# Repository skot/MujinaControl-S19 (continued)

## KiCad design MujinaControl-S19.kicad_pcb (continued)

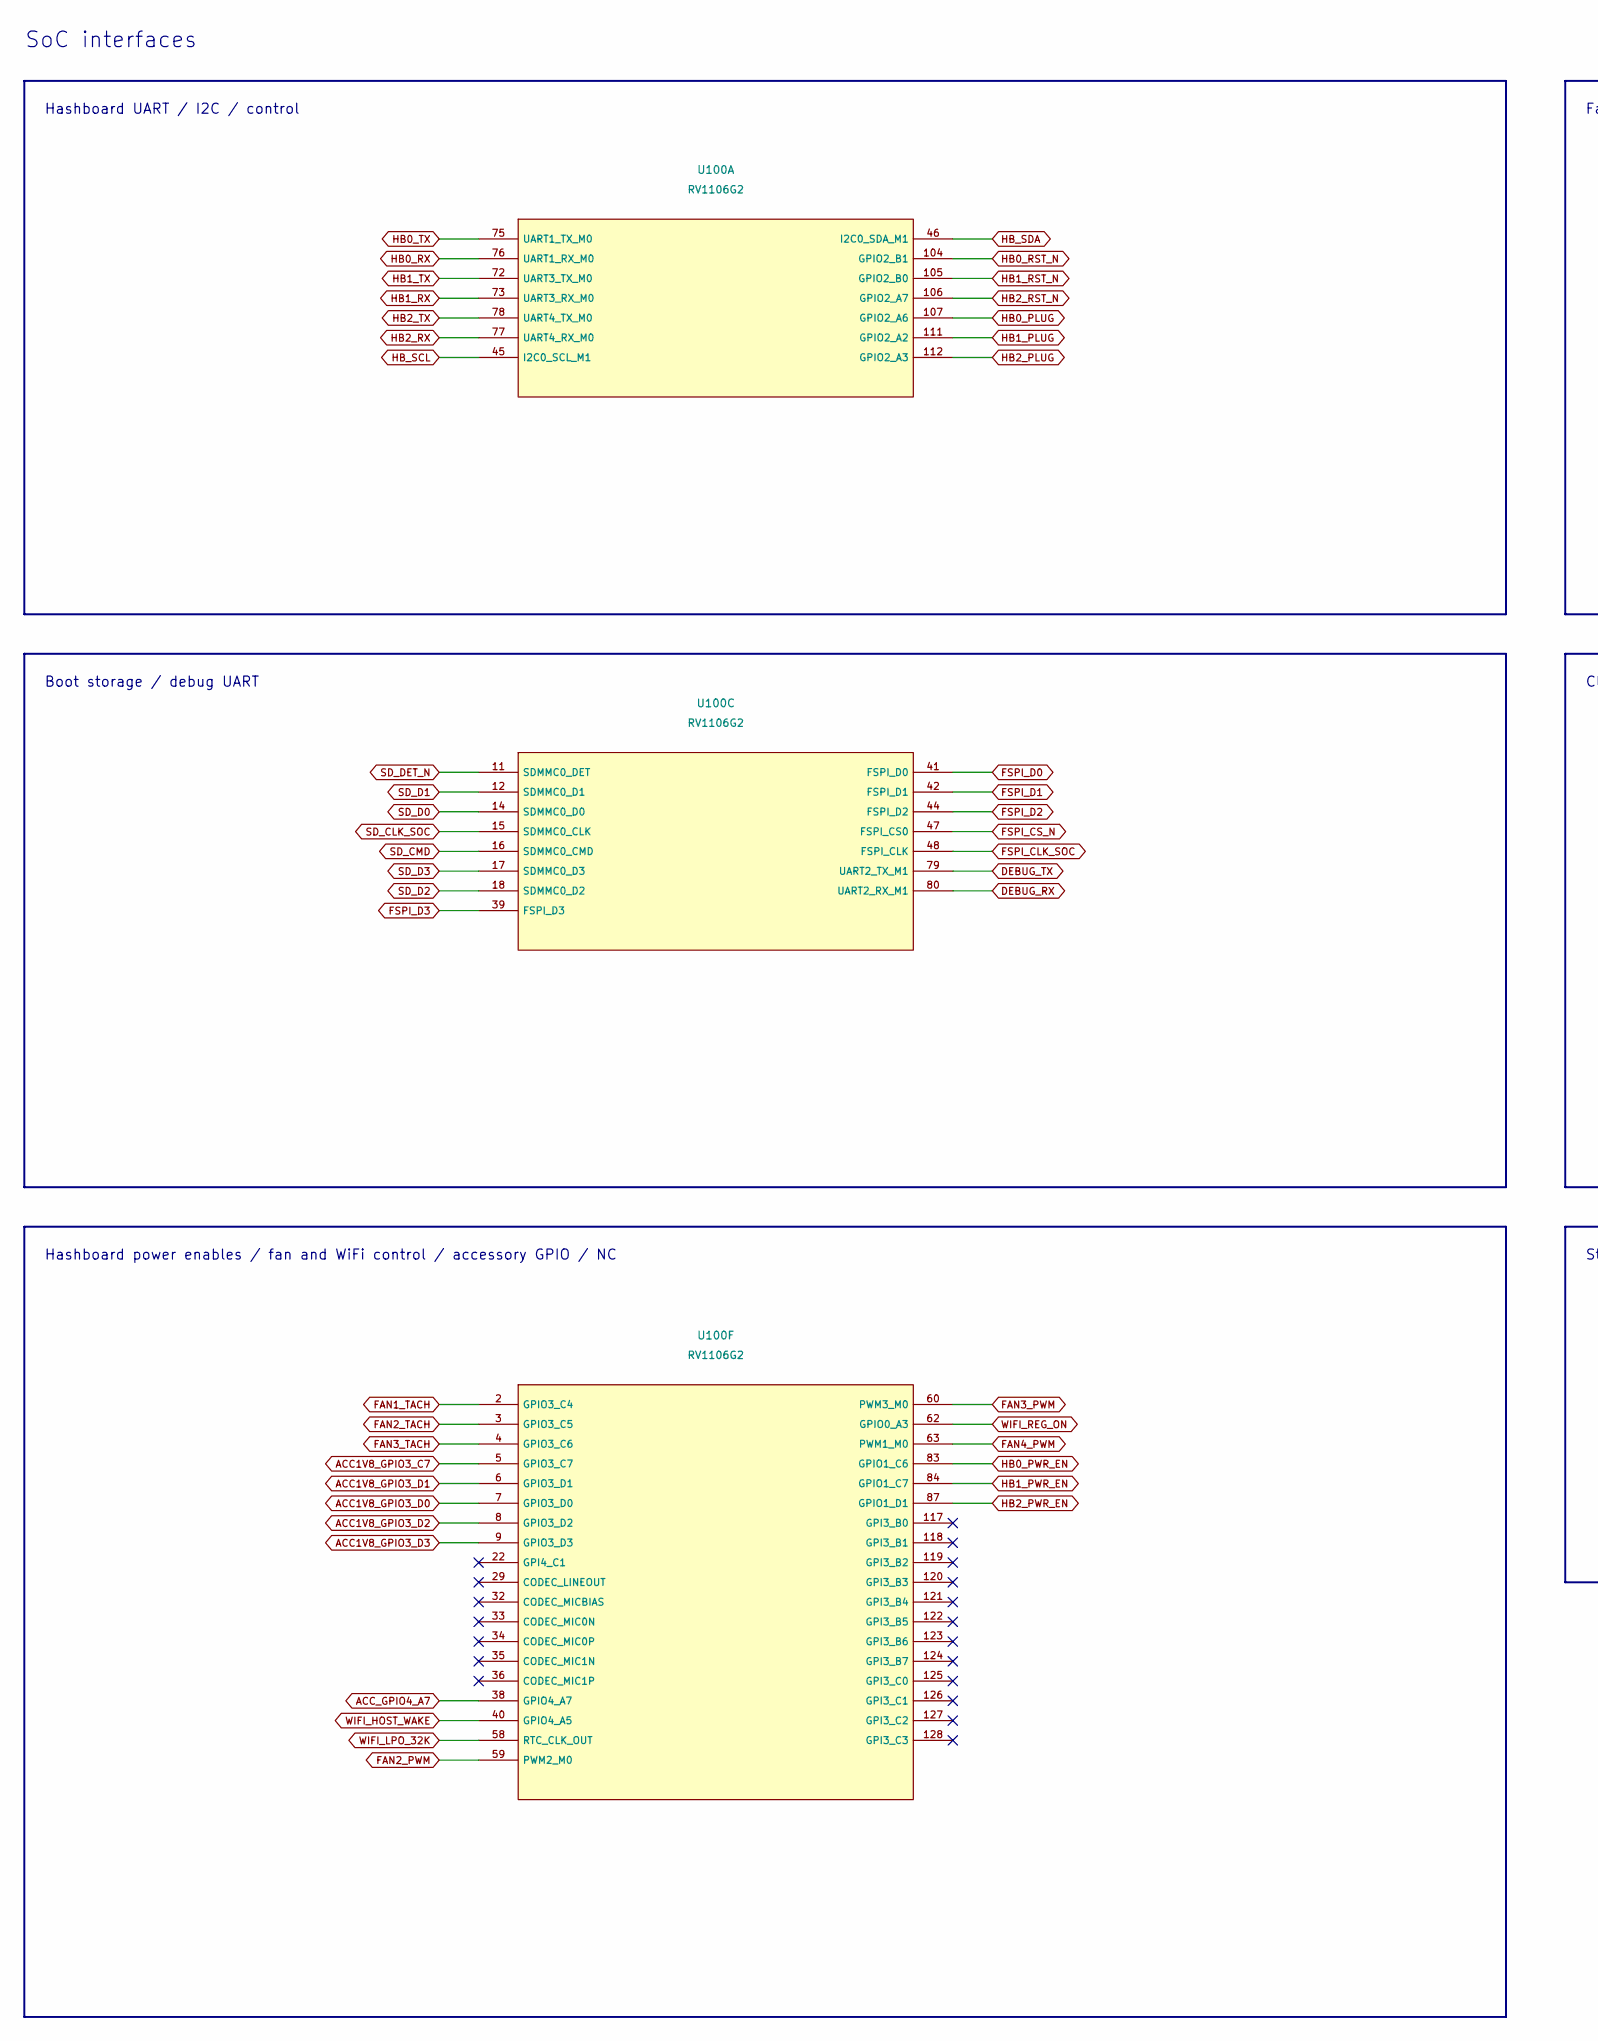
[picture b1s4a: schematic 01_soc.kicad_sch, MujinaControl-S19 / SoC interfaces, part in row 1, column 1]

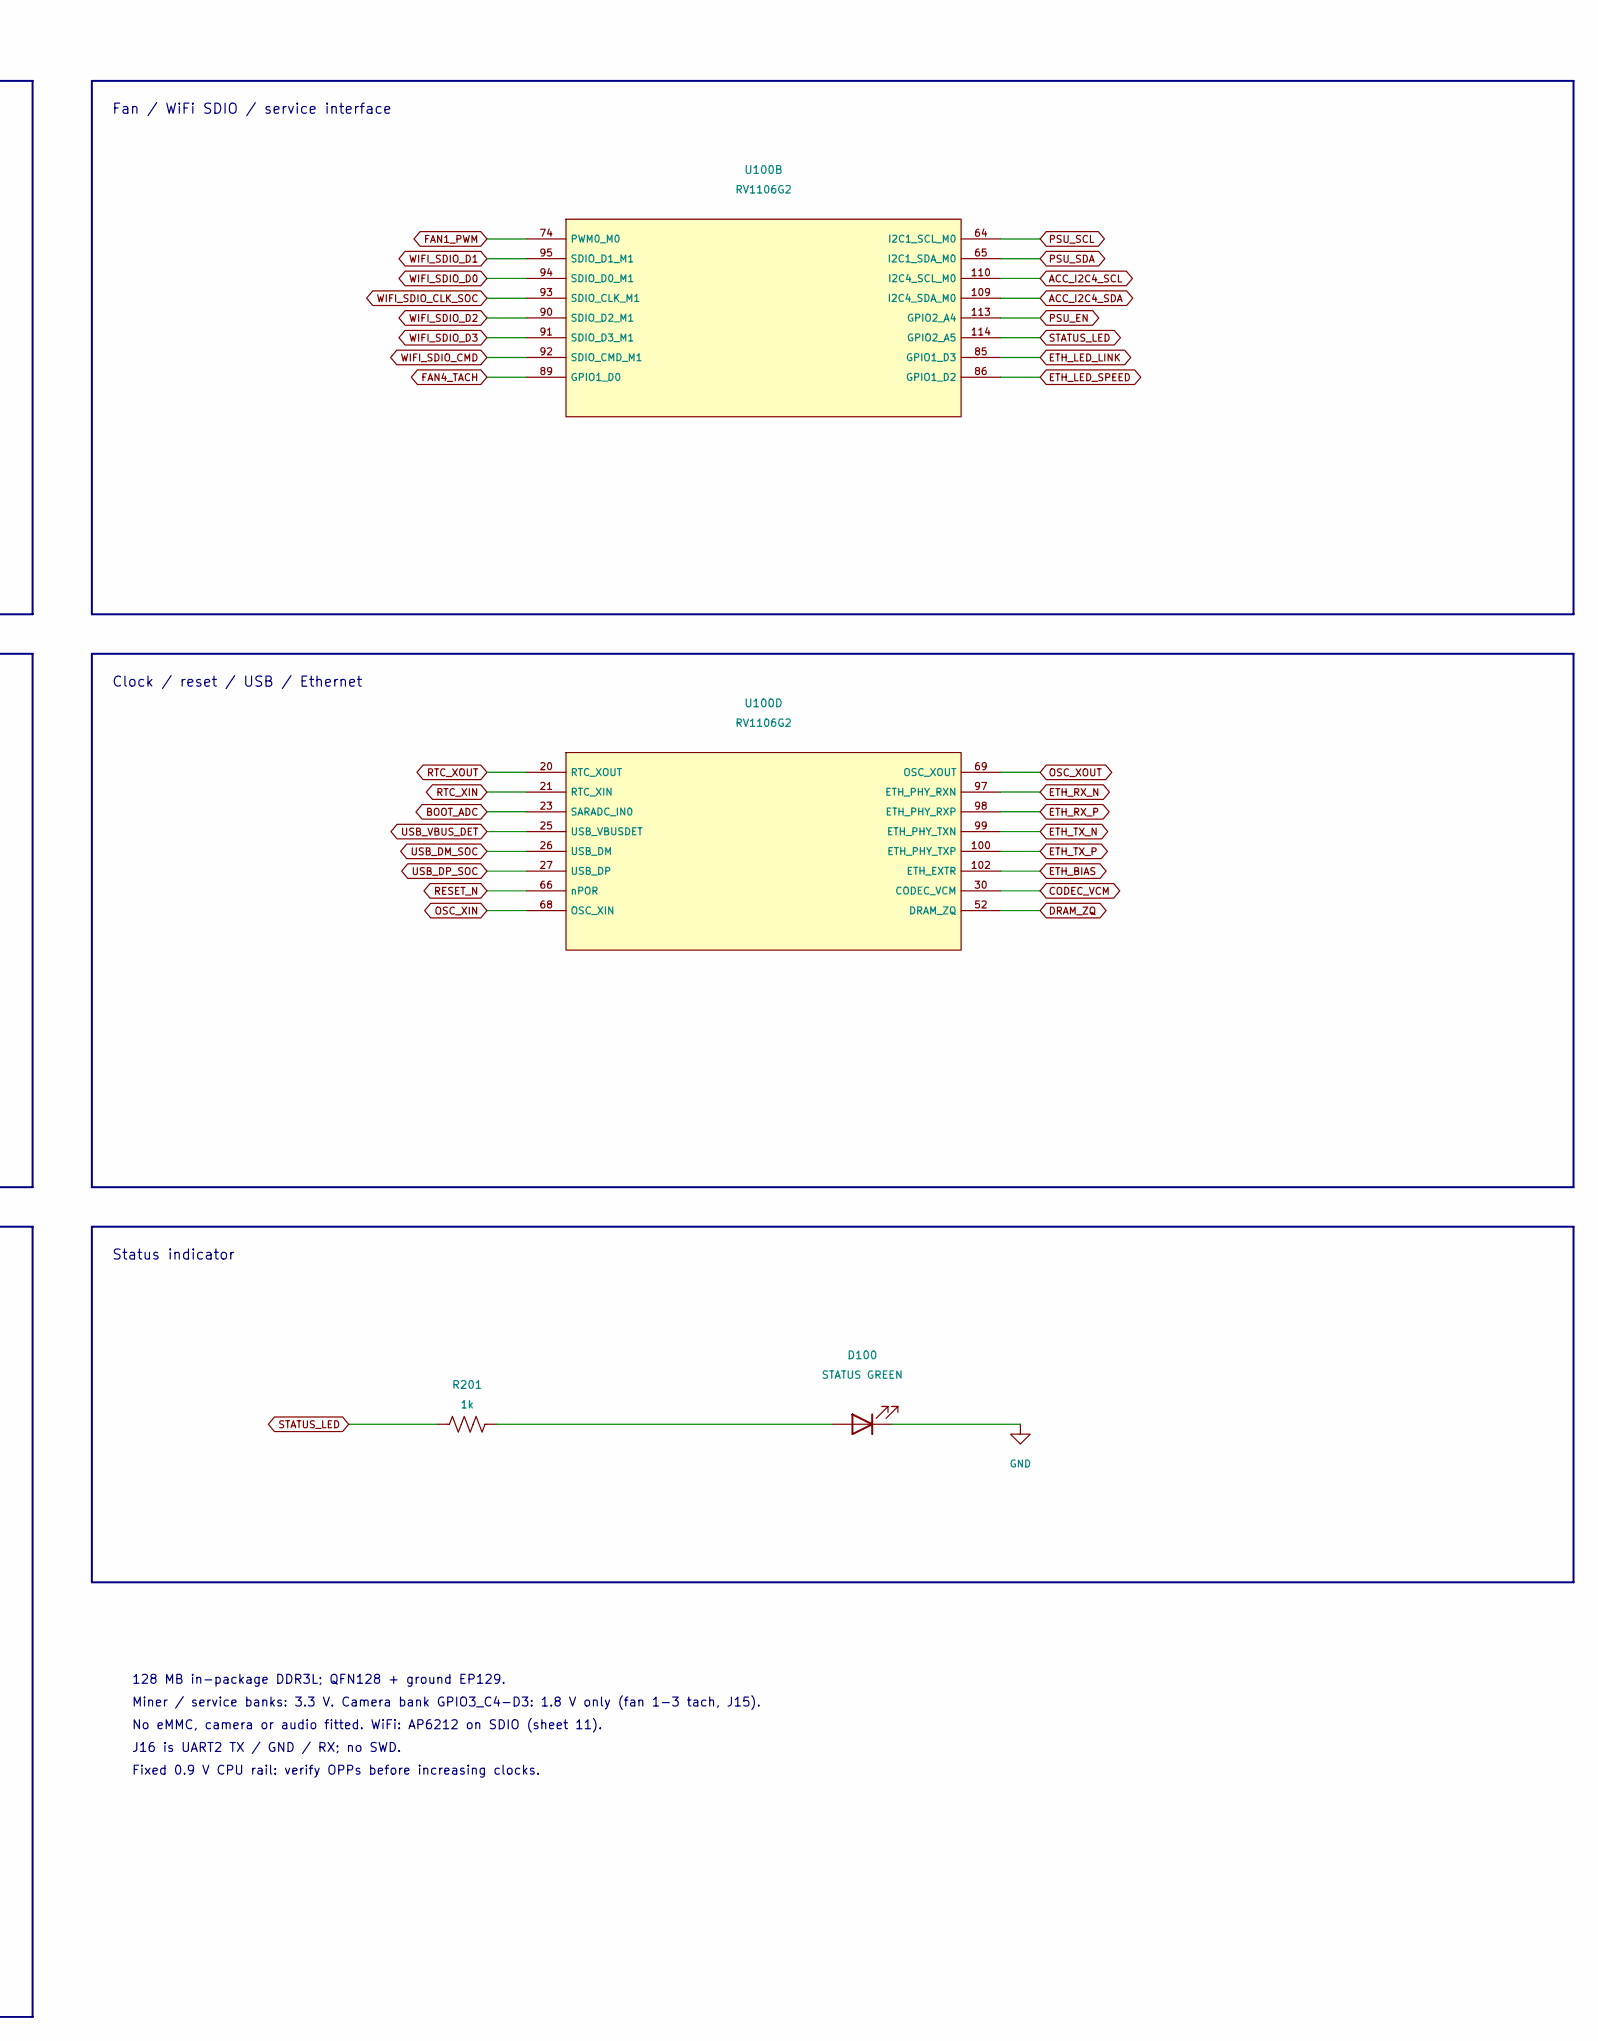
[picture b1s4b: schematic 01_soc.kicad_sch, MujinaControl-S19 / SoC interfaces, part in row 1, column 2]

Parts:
D100: STATUS GREEN; LED_0603_1608Metric; MPN LTST-C190KGKT; LCSC C125094
R201: 1k; R_0402_1005Metric; MPN 0402WGF1001TCE; LCSC C11702
U100: RV1106G2; Rockchip_QFN-128-1EP_12.3x12.3mm_P0.35mm_EP7x7mm; MPN RV1106G2; LCSC C5272606

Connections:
ACC1V8_GPIO3_C7: U100.5 (GPIO3_C7); also elsewhere on the board
ACC1V8_GPIO3_D0: U100.7 (GPIO3_D0); also elsewhere on the board
ACC1V8_GPIO3_D1: U100.6 (GPIO3_D1); also elsewhere on the board
ACC1V8_GPIO3_D2: U100.8 (GPIO3_D2); also elsewhere on the board
ACC1V8_GPIO3_D3: U100.9 (GPIO3_D3); also elsewhere on the board
ACC_GPIO4_A7: U100.38 (GPIO4_A7); also elsewhere on the board
ACC_I2C4_SCL: U100.110 (I2C4_SCL_M0); also elsewhere on the board
ACC_I2C4_SDA: U100.109 (I2C4_SDA_M0); also elsewhere on the board
BOOT_ADC: U100.23 (SARADC_IN0); also elsewhere on the board
CODEC_VCM: U100.30 (CODEC_VCM); also elsewhere on the board
DEBUG_RX: U100.80 (UART2_RX_M1); also elsewhere on the board
DEBUG_TX: U100.79 (UART2_TX_M1); also elsewhere on the board
DRAM_ZQ: U100.52 (DRAM_ZQ); also elsewhere on the board
ETH_BIAS: U100.102 (ETH_EXTR); also elsewhere on the board
ETH_LED_LINK: U100.85 (GPIO1_D3); also elsewhere on the board
ETH_LED_SPEED: U100.86 (GPIO1_D2); also elsewhere on the board
ETH_RX_N: U100.97 (ETH_PHY_RXN); also elsewhere on the board
ETH_RX_P: U100.98 (ETH_PHY_RXP); also elsewhere on the board
ETH_TX_N: U100.99 (ETH_PHY_TXN); also elsewhere on the board
ETH_TX_P: U100.100 (ETH_PHY_TXP); also elsewhere on the board
FAN1_PWM: U100.74 (PWM0_M0); also elsewhere on the board
FAN1_TACH: U100.2 (GPIO3_C4); also elsewhere on the board
FAN2_PWM: U100.59 (PWM2_M0); also elsewhere on the board
FAN2_TACH: U100.3 (GPIO3_C5); also elsewhere on the board
FAN3_PWM: U100.60 (PWM3_M0); also elsewhere on the board
FAN3_TACH: U100.4 (GPIO3_C6); also elsewhere on the board
FAN4_PWM: U100.63 (PWM1_M0); also elsewhere on the board
FAN4_TACH: U100.89 (GPIO1_D0); also elsewhere on the board
FSPI_CLK_SOC: U100.48 (FSPI_CLK); also elsewhere on the board
FSPI_CS_N: U100.47 (FSPI_CS0); also elsewhere on the board
FSPI_D0: U100.41 (FSPI_D0); also elsewhere on the board
FSPI_D1: U100.42 (FSPI_D1); also elsewhere on the board
FSPI_D2: U100.44 (FSPI_D2); also elsewhere on the board
FSPI_D3: U100.39 (FSPI_D3); also elsewhere on the board
GND: D100.1 (K); also elsewhere on the board
HB0_PLUG: U100.107 (GPIO2_A6); also elsewhere on the board
HB0_PWR_EN: U100.83 (GPIO1_C6); also elsewhere on the board
HB0_RST_N: U100.104 (GPIO2_B1); also elsewhere on the board
HB0_RX: U100.76 (UART1_RX_M0); also elsewhere on the board
HB0_TX: U100.75 (UART1_TX_M0); also elsewhere on the board
HB1_PLUG: U100.111 (GPIO2_A2); also elsewhere on the board
HB1_PWR_EN: U100.84 (GPIO1_C7); also elsewhere on the board
HB1_RST_N: U100.105 (GPIO2_B0); also elsewhere on the board
HB1_RX: U100.73 (UART3_RX_M0); also elsewhere on the board
HB1_TX: U100.72 (UART3_TX_M0); also elsewhere on the board
HB2_PLUG: U100.112 (GPIO2_A3); also elsewhere on the board
HB2_PWR_EN: U100.87 (GPIO1_D1); also elsewhere on the board
HB2_RST_N: U100.106 (GPIO2_A7); also elsewhere on the board
HB2_RX: U100.77 (UART4_RX_M0); also elsewhere on the board
HB2_TX: U100.78 (UART4_TX_M0); also elsewhere on the board
HB_SCL: U100.45 (I2C0_SCL_M1); also elsewhere on the board
HB_SDA: U100.46 (I2C0_SDA_M1); also elsewhere on the board
unnamed: D100.2 (A), R201.2
OSC_XIN: U100.68 (OSC_XIN); also elsewhere on the board
OSC_XOUT: U100.69 (OSC_XOUT); also elsewhere on the board
PSU_EN: U100.113 (GPIO2_A4); also elsewhere on the board
PSU_SCL: U100.64 (I2C1_SCL_M0); also elsewhere on the board
PSU_SDA: U100.65 (I2C1_SDA_M0); also elsewhere on the board
RESET_N: U100.66 (nPOR); also elsewhere on the board
RTC_XIN: U100.21 (RTC_XIN); also elsewhere on the board
RTC_XOUT: U100.20 (RTC_XOUT); also elsewhere on the board
SD_CLK_SOC: U100.15 (SDMMC0_CLK); also elsewhere on the board
SD_CMD: U100.16 (SDMMC0_CMD); also elsewhere on the board
SD_D0: U100.14 (SDMMC0_D0); also elsewhere on the board
SD_D1: U100.12 (SDMMC0_D1); also elsewhere on the board
SD_D2: U100.18 (SDMMC0_D2); also elsewhere on the board
SD_D3: U100.17 (SDMMC0_D3); also elsewhere on the board
SD_DET_N: U100.11 (SDMMC0_DET); also elsewhere on the board
STATUS_LED: R201.1, U100.114 (GPIO2_A5)
USB_DM_SOC: U100.26 (USB_DM); also elsewhere on the board
USB_DP_SOC: U100.27 (USB_DP); also elsewhere on the board
USB_VBUS_DET: U100.25 (USB_VBUSDET); also elsewhere on the board
WIFI_HOST_WAKE: U100.40 (GPIO4_A5); also elsewhere on the board
WIFI_LPO_32K: U100.58 (RTC_CLK_OUT); also elsewhere on the board
WIFI_REG_ON: U100.62 (GPIO0_A3); also elsewhere on the board
WIFI_SDIO_CLK_SOC: U100.93 (SDIO_CLK_M1); also elsewhere on the board
WIFI_SDIO_CMD: U100.92 (SDIO_CMD_M1); also elsewhere on the board
WIFI_SDIO_D0: U100.94 (SDIO_D0_M1); also elsewhere on the board
WIFI_SDIO_D1: U100.95 (SDIO_D1_M1); also elsewhere on the board
WIFI_SDIO_D2: U100.90 (SDIO_D2_M1); also elsewhere on the board
WIFI_SDIO_D3: U100.91 (SDIO_D3_M1); also elsewhere on the board

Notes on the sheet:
Clock / reset / USB / Ethernet
Status indicator
Fixed 0.9 V CPU rail: verify OPPs before increasing clocks.
Miner / service banks: 3.3 V. Camera bank GPIO3_C4-D3: 1.8 V only (fan 1-3 tach, J15).
Hashboard UART / I2C / control
No eMMC, camera or audio fitted. WiFi: AP6212 on SDIO (sheet 11).
Boot storage / debug UART
Hashboard power enables / fan and WiFi control / accessory GPIO / NC
J16 is UART2 TX / GND / RX; no SWD.
Fan / WiFi SDIO / service interface
128 MB in-package DDR3L; QFN128 + ground EP129.
SoC interfaces

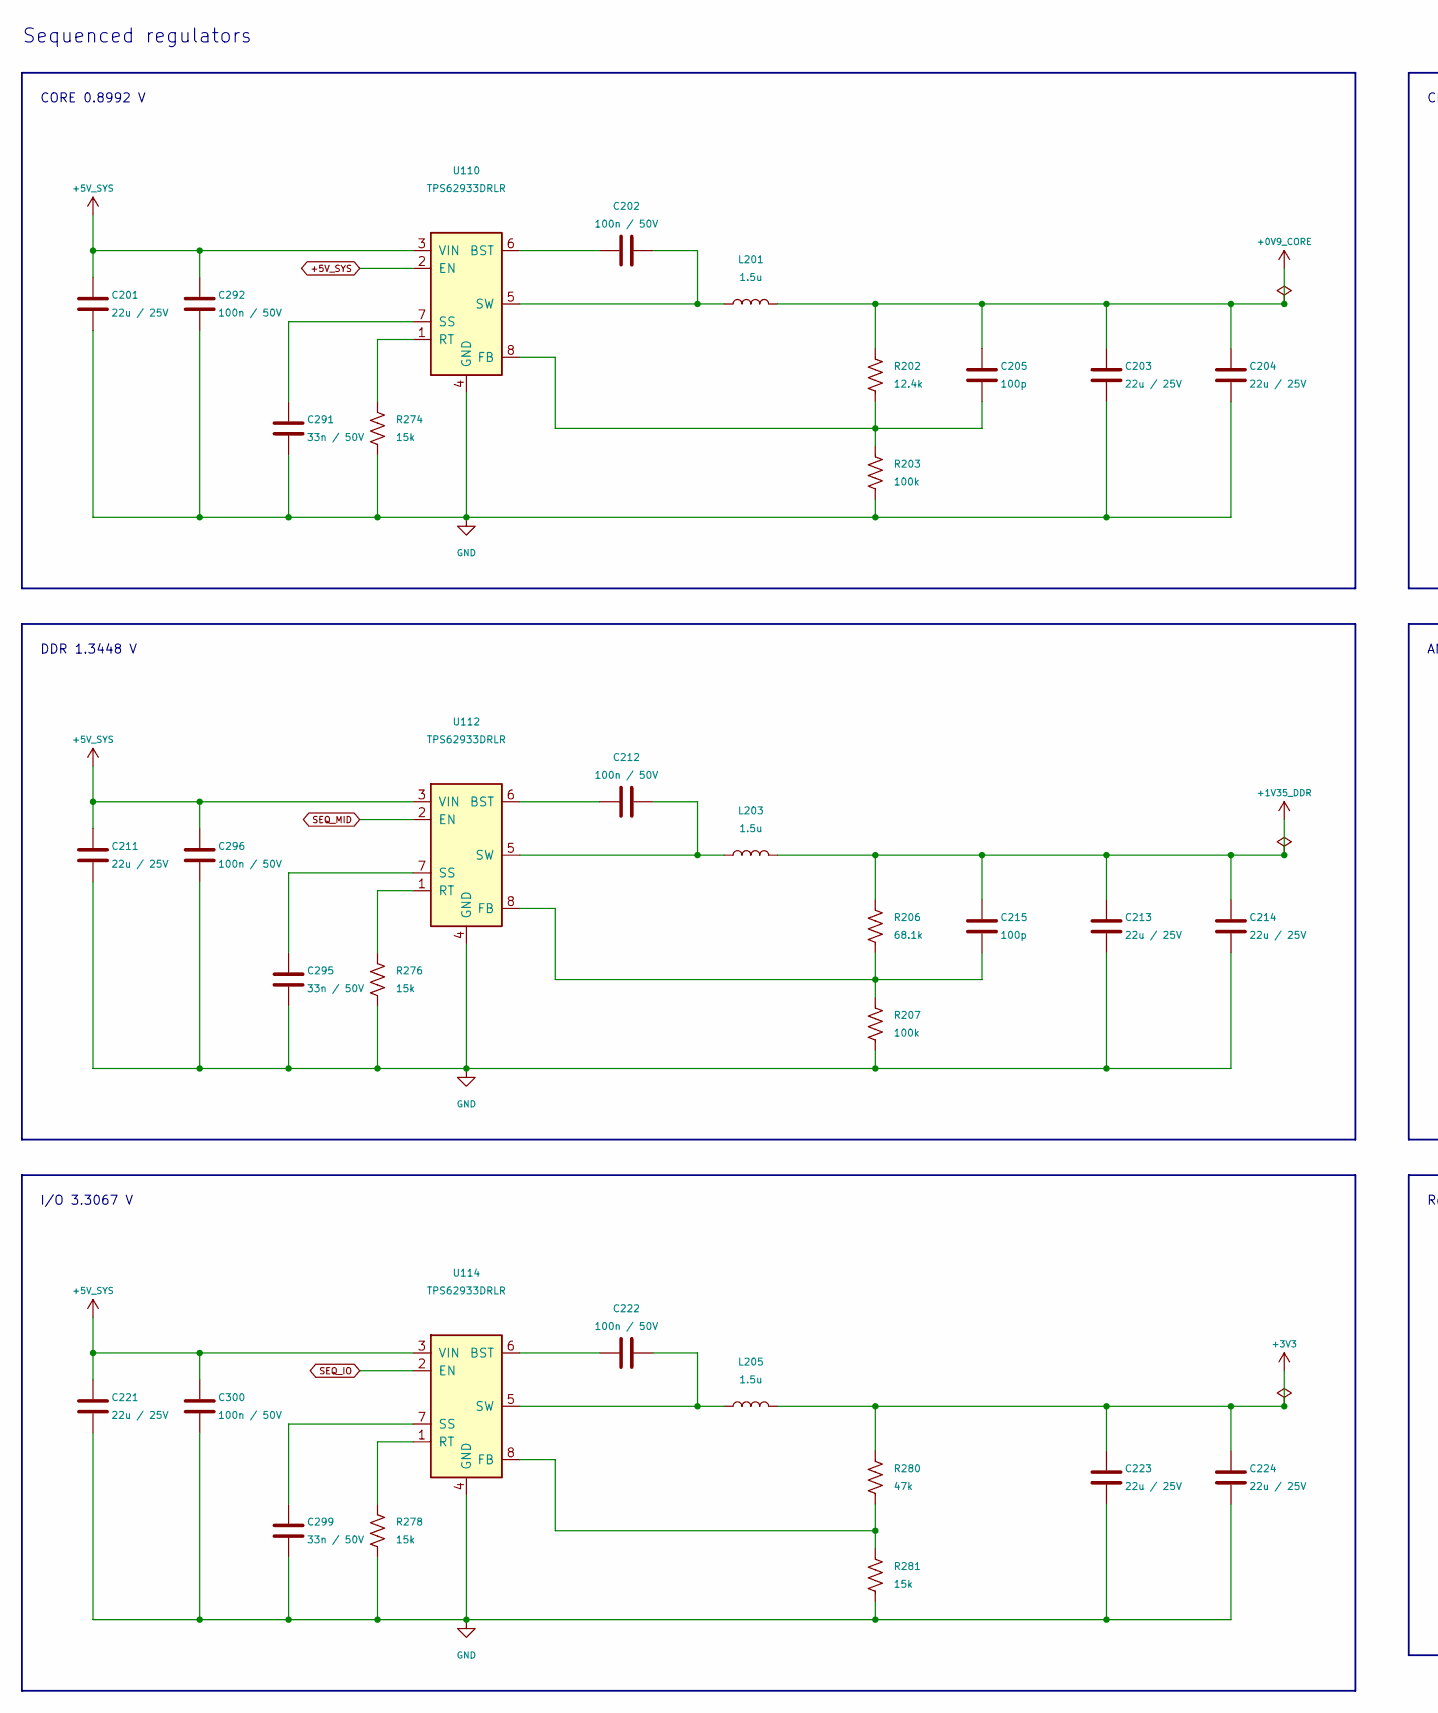
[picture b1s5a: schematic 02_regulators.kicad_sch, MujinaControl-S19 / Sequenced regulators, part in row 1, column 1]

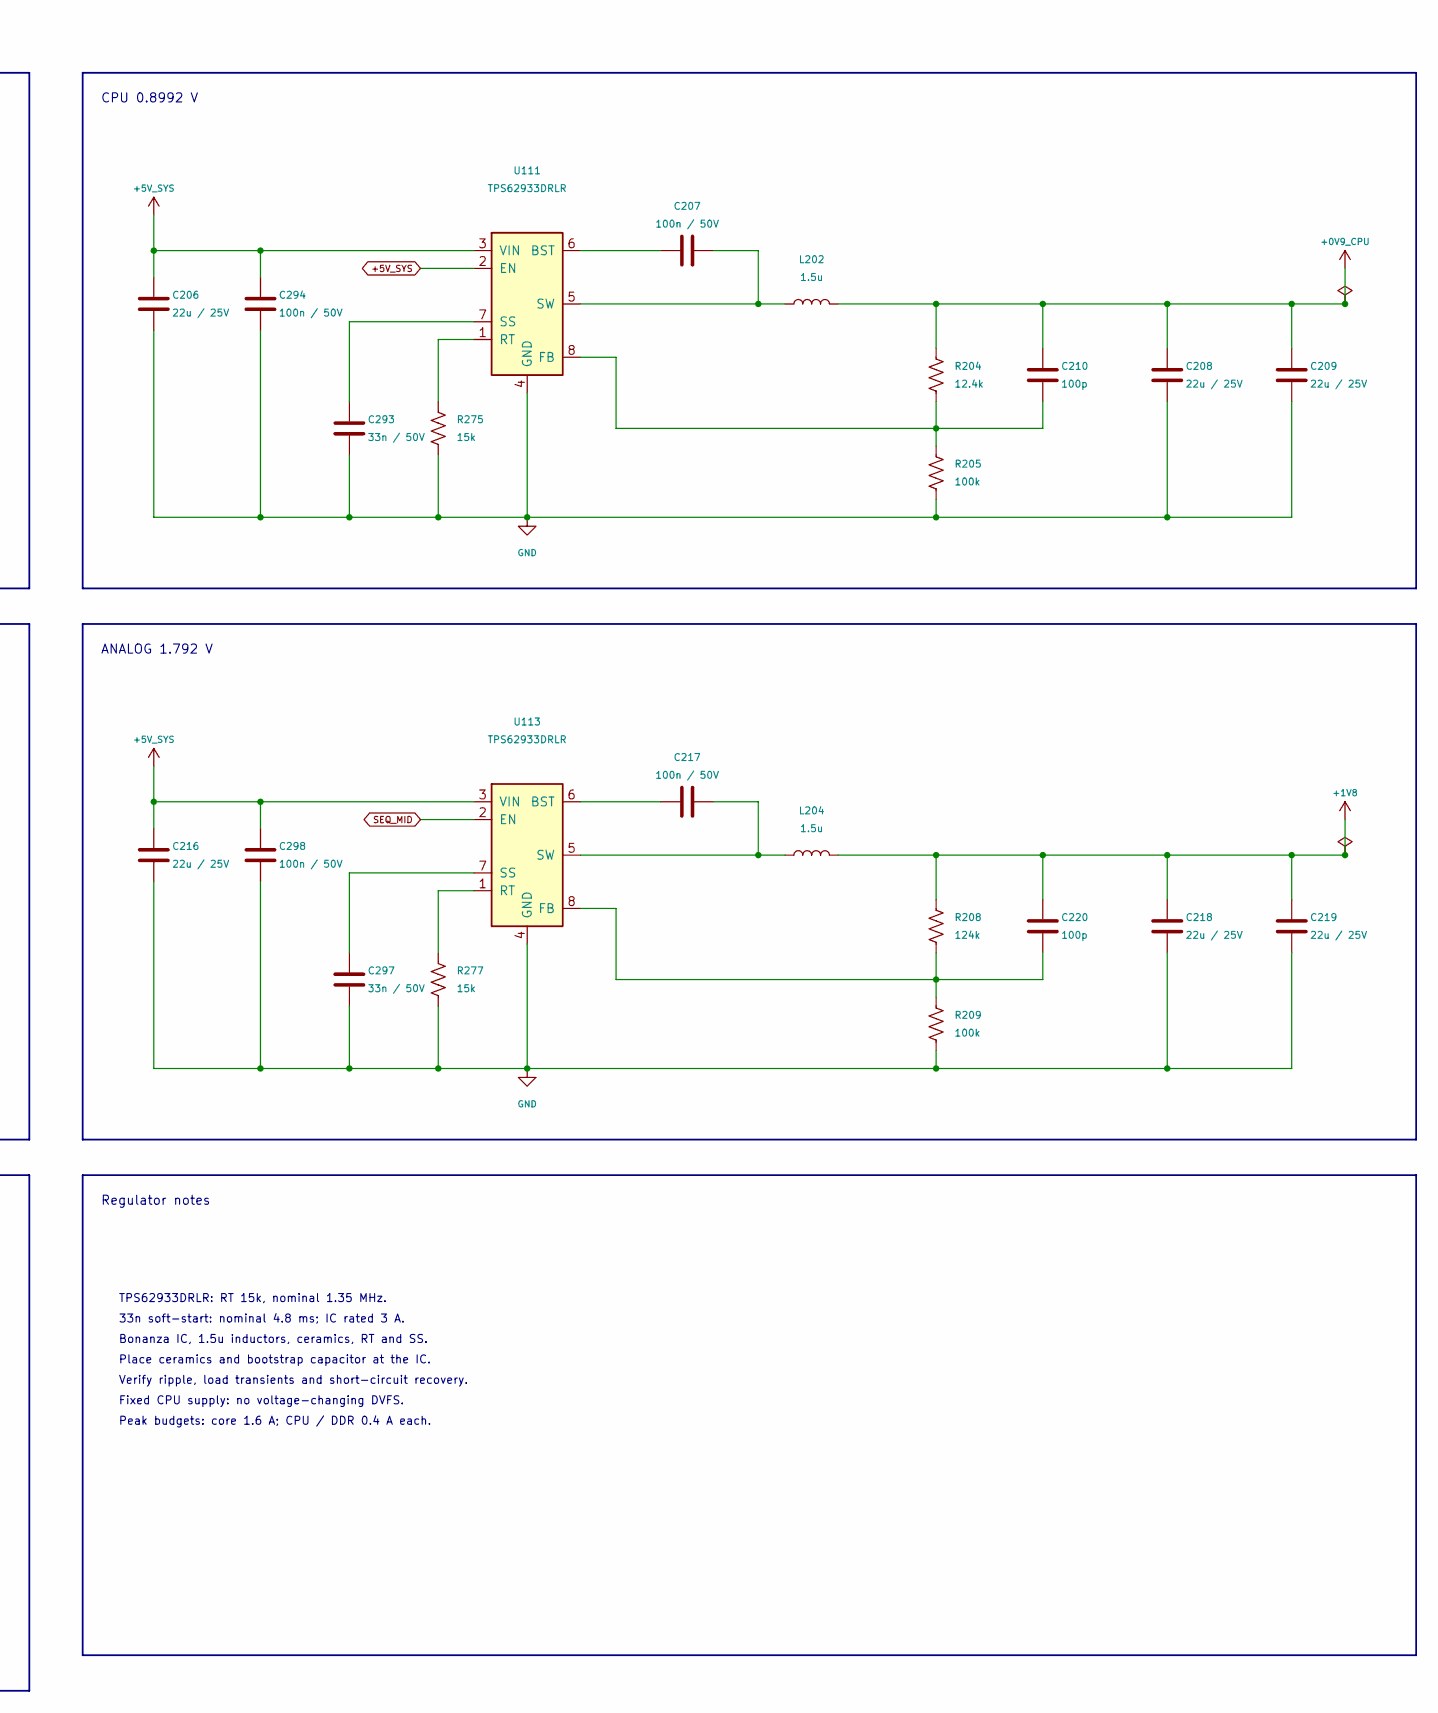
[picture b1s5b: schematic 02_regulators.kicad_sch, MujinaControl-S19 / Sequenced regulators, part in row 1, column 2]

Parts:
C201, C203, C204, C206, C208, C209, C211, C213, C214, C216, C218, C219, C221, C223, C224: 22u / 25V; C_0805_2012Metric; MPN CL21A226MAQNNNE; LCSC C45783
C202, C207, C212, C217, C222, C292, C294, C296, C298, C300: 100n / 50V; C_0402_1005Metric; MPN CL05B104KB54PNC; LCSC C307331
C205, C210, C215, C220: 100p; C_0402_1005Metric; MPN 0402CG101J500NT; LCSC C1546
C291, C293, C295, C297, C299: 33n / 50V; C_0603_1608Metric; MPN CL10B333KB8NNNC; LCSC C21117
L201, L202, L203, L204, L205: 1.5u; IND-SMD_L2.0-W1.6; MPN FTC201612S1R5MBCA; LCSC C5832350
R202, R204: 12.4k; R_0402_1005Metric; MPN RC0402FR-0712K4L; LCSC C138060
R203, R205, R207, R209: 100k; R_0402_1005Metric; MPN 0402WGF1003TCE; LCSC C25741
R206: 68.1k; R_0402_1005Metric; MPN RC0402FR-0768K1L; LCSC C276276
R208: 124k; R_0402_1005Metric; MPN 0402WGF1243TCE; LCSC C36777
R274, R275, R276, R277, R278, R281: 15k; R_0402_1005Metric; MPN 0402WGF1502TCE; LCSC C25756
R280: 47k; R_0402_1005Metric; MPN 0402WGF4702TCE; LCSC C25792
U110, U111, U112, U113, U114: TPS62933DRLR; SOT-583-8_L2.1-W1.2-P0.50-LS1.6-BR; MPN TPS62933DRLR; LCSC C3200405

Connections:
+0V9_CORE: C203.1, C204.1, C205.1, L201.2, R202.1; also elsewhere on the board
+0V9_CPU: C208.1, C209.1, C210.1, L202.2, R204.1; also elsewhere on the board
+1V8: C218.1, C219.1, C220.1, L204.2, R208.1; also elsewhere on the board
+1V35_DDR: C213.1, C214.1, C215.1, L203.2, R206.1; also elsewhere on the board
+3V3: C223.1, C224.1, L205.2, R280.1; also elsewhere on the board
+5V_SYS: C201.1, C206.1, C211.1, C216.1, C221.1, C292.1, C294.1, C296.1, C298.1, C300.1, U110.2 (EN), U110.3 (VIN), U111.2 (EN), U111.3 (VIN), U112.3 (VIN), U113.3 (VIN), U114.3 (VIN); also elsewhere on the board
GND: C201.2, C203.2, C204.2, C206.2, C208.2, C209.2, C211.2, C213.2, C214.2, C216.2, C218.2, C219.2, C221.2, C223.2, C224.2, C291.2, C292.2, C293.2, C294.2, C295.2, C296.2, C297.2, C298.2, C299.2, C300.2, R203.2, R205.2, R207.2, R209.2, R274.2, R275.2, R276.2, R277.2, R278.2, R281.2, U110.4 (GND), U111.4 (GND), U112.4 (GND), U113.4 (GND), U114.4 (GND); also elsewhere on the board
unnamed: C202.1, U110.6 (BST)
unnamed: C205.2, R202.2, R203.1, U110.8 (FB)
unnamed: R274.1, U110.1 (RT)
unnamed: C291.1, U110.7 (SS)
unnamed: C202.2, L201.1, U110.5 (SW)
unnamed: C207.1, U111.6 (BST)
unnamed: C210.2, R204.2, R205.1, U111.8 (FB)
unnamed: R275.1, U111.1 (RT)
unnamed: C293.1, U111.7 (SS)
unnamed: C207.2, L202.1, U111.5 (SW)
unnamed: C212.1, U112.6 (BST)
unnamed: C215.2, R206.2, R207.1, U112.8 (FB)
unnamed: R276.1, U112.1 (RT)
unnamed: C295.1, U112.7 (SS)
unnamed: C212.2, L203.1, U112.5 (SW)
unnamed: C217.1, U113.6 (BST)
unnamed: C220.2, R208.2, R209.1, U113.8 (FB)
unnamed: R277.1, U113.1 (RT)
unnamed: C297.1, U113.7 (SS)
unnamed: C217.2, L204.1, U113.5 (SW)
unnamed: C222.1, U114.6 (BST)
unnamed: R280.2, R281.1, U114.8 (FB)
unnamed: R278.1, U114.1 (RT)
unnamed: C299.1, U114.7 (SS)
unnamed: C222.2, L205.1, U114.5 (SW)
SEQ_IO: U114.2 (EN); also elsewhere on the board
SEQ_MID: U112.2 (EN), U113.2 (EN); also elsewhere on the board

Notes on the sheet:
CPU 0.8992 V
DDR 1.3448 V
Peak budgets: core 1.6 A; CPU / DDR 0.4 A each.
CORE 0.8992 V
Verify ripple, load transients and short-circuit recovery.
ANALOG 1.792 V
Place ceramics and bootstrap capacitor at the IC.
Bonanza IC, 1.5u inductors, ceramics, RT and SS.
Sequenced regulators
I/O 3.3067 V
Fixed CPU supply: no voltage-changing DVFS.
TPS62933DRLR: RT 15k, nominal 1.35 MHz.
Regulator notes
33n soft-start: nominal 4.8 ms; IC rated 3 A.
